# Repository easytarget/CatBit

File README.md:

# BBC Micro:Bit Cat Entertainer

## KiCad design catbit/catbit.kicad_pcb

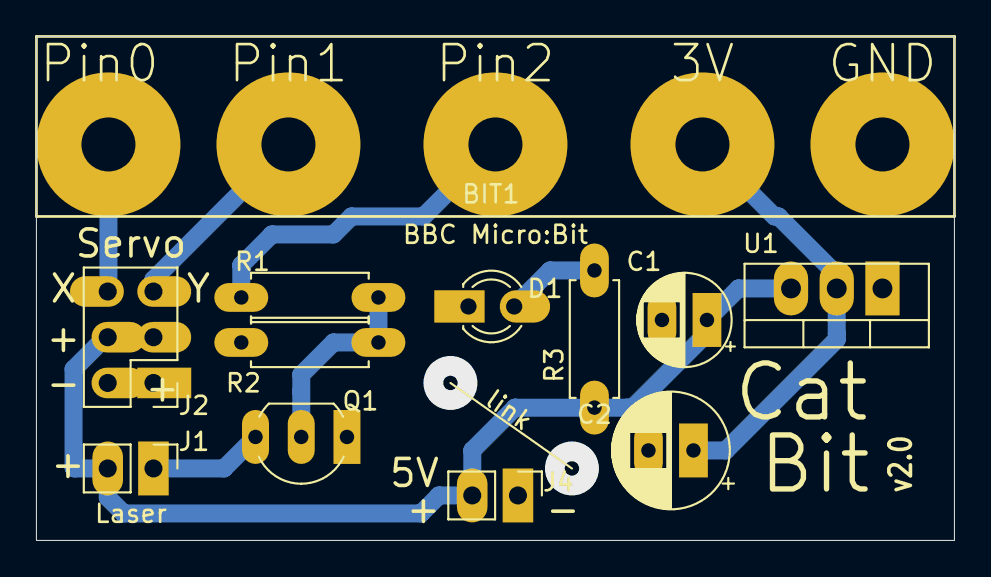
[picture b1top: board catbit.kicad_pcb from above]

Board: 2 copper layers, 51.0 x 28.0 mm, 12 parts (0 on the bottom side), 9 nets.

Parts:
BIT1: BBC-MicroBit; MicroBit
C1: 10uF; CP_Radial_D5.0mm_P2.50mm
C2: 100uF; CP_Radial_D6.3mm_P2.50mm
D1: Pwr; LED_D3.0mm
J1: 5V LED Laser; PinHeader_1x02_P2.54mm_Vertical
J2: Servos; PinHeader_2x03_P2.54mm_Vertical
J4: 5V DC in; PinHeader_1x02_P2.54mm_Vertical
Q1: 2N7000; TO-92_Inline_Wide
R1: 220R; R_Axial_DIN0207_L6.3mm_D2.5mm_P7.62mm_Horizontal
R2: 10K; R_Axial_DIN0207_L6.3mm_D2.5mm_P7.62mm_Horizontal
R3: 330R; R_Axial_DIN0207_L6.3mm_D2.5mm_P7.62mm_Horizontal
U1: LD33; TO-220-3_Vertical

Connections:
3V: BIT1.2, C2.1, U1.2
5V: C1.1, J1.2, J2.3, J2.4, J4.2, R3.2, U1.3
GND: BIT1.1, C1.2, C2.2, D1.1, J2.1, J2.2, J4.1, Q1.1, R2.1, U1.1
LASER: BIT1.3, R1.2
unnamed: D1.2, R3.1
unnamed: J1.1, Q1.3
unnamed: Q1.2, R1.1, R2.2
X: BIT1.5, J2.6
Y: BIT1.4, J2.5

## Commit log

2020-04-28 The CatBit. KiCad project is complete
2020-04-29 A case
2020-04-29 Case, rendered
2020-04-29 Updates following test print, and a good think
2020-04-29 Demo loop for microbit
2020-04-29 A better demo.
2020-04-29 Revised (V2) PCB with led.
2020-04-30 Minor silkscreen mod and move aux. axis to bottom-left corner (easier to set up cnc)
2020-04-30 A better example, self-contained but not very cat entertaining
2020-04-30 Laser as a class with quadratic power mapping, other demo bits
2020-05-01 Some sort of progress :-)
2020-05-02 A working demo with cat entertainment and movement
2020-05-02 The new, improved, servo demo (needs finishing)
2020-05-02 Another checkpoint, even will work automatically now
2020-05-02 Improved movement between points, 1.3 hour intervals between random plays
2020-05-03 Better defaults, movement handler improvements
2020-05-05 Beta Release * light sensing * timer on off * animations, countdowns and progress indicator * separate libraries
2020-05-11 catchup with comments and some images
